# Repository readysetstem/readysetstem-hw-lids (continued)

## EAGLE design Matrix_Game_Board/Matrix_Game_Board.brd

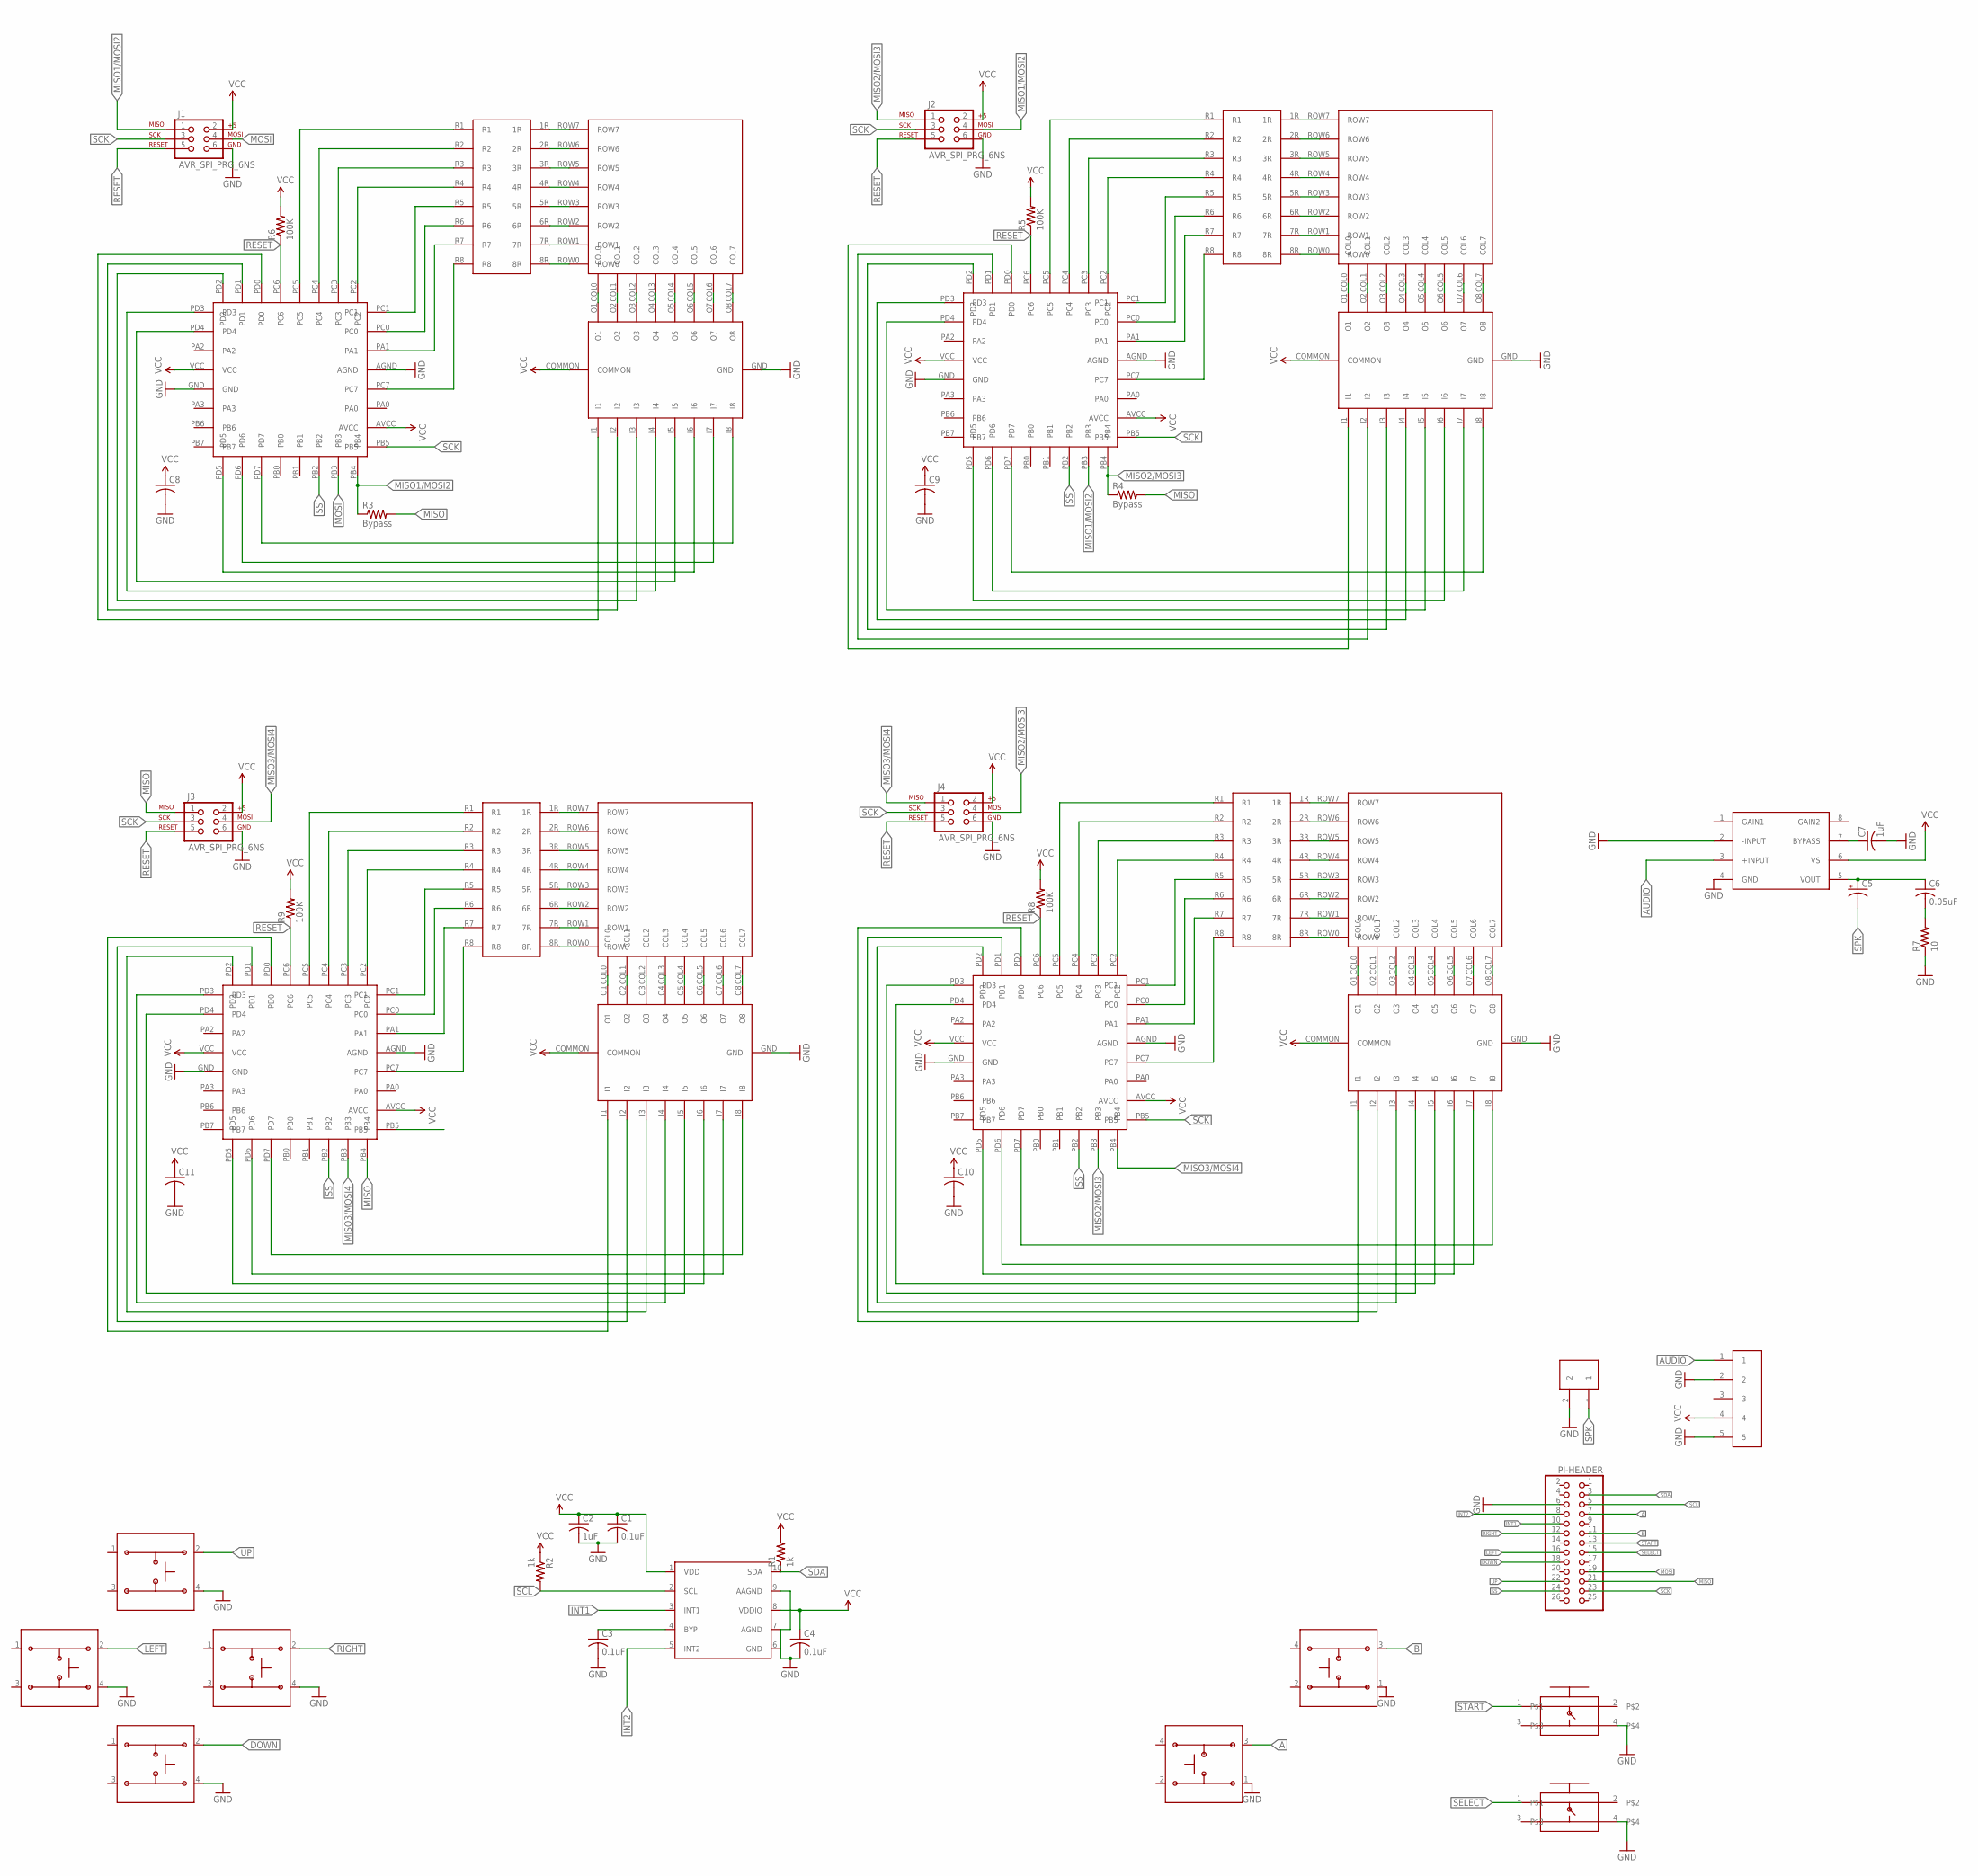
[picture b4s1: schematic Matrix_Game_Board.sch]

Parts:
C1, C3, C4: 0.1uF; C0603
C2, C7: 1uF; C0603
C5: CPOL-US153CLV-0605; 153CLV-0605
C6: 0.05uF; C0603
C8, C9, C10, C11: C-USC0603; C0603
J1, J2, J3, J4: AVR_SPI_PRG_6NS; 2X3-NS
PI-HEADER: PINHD-2X13; 2X13
R1, R2: 1k; R0603
R3, R4: Bypass; R0603
R5, R6, R8, R9: 100K; R0603
R7: 10; R0603
U$1, U$3, U$8, U$13: 8X8_LED_MATRIX
U$2, U$7, U$12, U$16: RES_ARRAY
U$4, U$5, U$10, U$14: ULN2803AFWG
U$6, U$9, U$11, U$15: ATTINY48
U$17, U$18, U$19, U$20, U$21, U$22: 12X12MM_BUTTON
U$23: MMA8653FCR1
U$24, U$26: SMDTACTILE
U$25: LM386
U$29: DF3_1X2
U$30: DF3_1X5

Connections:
A: PI-HEADER.7, U$22.3
AUDIO: U$25.3 (+INPUT), U$30.1
B: PI-HEADER.11, U$21.3
DOWN: PI-HEADER.18, U$20.2
GND: C1.2, C2.2, C3.2, C4.2, C7.2, C8.2, C9.2, C10.2, C11.2, J1.6, J2.6, J3.6, J4.6, PI-HEADER.6, R7.1, U$4.GND, U$5.GND, U$6.AGND, U$6.GND, U$9.AGND, U$9.GND, U$10.GND, U$11.AGND, U$11.GND, U$14.GND, U$15.AGND, U$15.GND, U$17.4, U$18.4, U$19.4, U$20.4, U$21.1, U$22.1, U$23.6 (GND), U$23.7 (AGND), U$23.9 (AAGND), U$24.4, U$25.2 (-INPUT), U$25.4 (GND), U$26.4, U$29.2, U$30.2, U$30.5
INT1: PI-HEADER.10, U$23.3 (INT1)
INT2: PI-HEADER.8, U$23.5 (INT2)
LEFT: PI-HEADER.16, U$18.2
MISO: J3.1, PI-HEADER.21, R3.2, R4.2, U$11.PB4
MISO1/MOSI2: J1.1, J2.4, R3.1, U$6.PB3, U$9.PB4
MISO2/MOSI3: J2.1, J4.4, R4.1, U$6.PB4, U$15.PB3
MISO3/MOSI4: J3.4, J4.1, U$11.PB3, U$15.PB4
MOSI: J1.4, PI-HEADER.19, U$9.PB3
unnamed: U$1.COL0, U$5.O1
unnamed: U$1.COL1, U$5.O2
unnamed: U$1.COL2, U$5.O3
unnamed: U$1.COL3, U$5.O4
unnamed: U$1.COL4, U$5.O5
unnamed: U$1.COL5, U$5.O6
unnamed: U$1.COL6, U$5.O7
unnamed: U$1.COL7, U$5.O8
unnamed: U$1.ROW7, U$2.1R
unnamed: U$1.ROW6, U$2.2R
unnamed: U$1.ROW5, U$2.3R
unnamed: U$1.ROW4, U$2.4R
unnamed: U$1.ROW3, U$2.5R
unnamed: U$1.ROW2, U$2.6R
unnamed: U$1.ROW1, U$2.7R
unnamed: U$1.ROW0, U$2.8R
unnamed: U$5.I1, U$9.PD0
unnamed: U$5.I2, U$9.PD1
unnamed: U$5.I3, U$9.PD2
unnamed: U$5.I4, U$9.PD3
unnamed: U$5.I5, U$9.PD4
unnamed: U$5.I6, U$9.PD5
unnamed: U$5.I7, U$9.PD6
unnamed: U$5.I8, U$9.PD7
unnamed: U$2.R7, U$9.PA1
unnamed: U$2.R8, U$9.PC7
unnamed: U$2.R6, U$9.PC0
unnamed: U$2.R5, U$9.PC1
unnamed: U$2.R4, U$9.PC2
unnamed: U$2.R3, U$9.PC3
unnamed: U$2.R2, U$9.PC4
unnamed: U$2.R1, U$9.PC5
unnamed: C7.1, U$25.7 (BYPASS)
unnamed: C3.1, U$23.4 (BYP)
unnamed: C5.+, C6.1, U$25.5 (VOUT)
unnamed: U$3.COL0, U$4.O1
unnamed: C6.2, R7.2
unnamed: U$3.COL1, U$4.O2
unnamed: U$3.COL2, U$4.O3
unnamed: U$3.COL3, U$4.O4
unnamed: U$3.COL4, U$4.O5
unnamed: U$3.COL5, U$4.O6
unnamed: U$3.COL6, U$4.O7
unnamed: U$3.COL7, U$4.O8
unnamed: U$3.ROW7, U$7.1R
unnamed: U$3.ROW6, U$7.2R
unnamed: U$3.ROW5, U$7.3R
unnamed: U$3.ROW4, U$7.4R
unnamed: U$3.ROW3, U$7.5R
unnamed: U$3.ROW2, U$7.6R
unnamed: U$3.ROW1, U$7.7R
unnamed: U$3.ROW0, U$7.8R
unnamed: U$4.I1, U$6.PD0
unnamed: U$4.I2, U$6.PD1
unnamed: U$4.I3, U$6.PD2
unnamed: U$4.I4, U$6.PD3
unnamed: U$4.I5, U$6.PD4
unnamed: U$4.I6, U$6.PD5
unnamed: U$4.I7, U$6.PD6
unnamed: U$4.I8, U$6.PD7
unnamed: U$6.PA1, U$7.R7
unnamed: U$6.PC7, U$7.R8
unnamed: U$6.PC0, U$7.R6
unnamed: U$6.PC1, U$7.R5
unnamed: U$6.PC2, U$7.R4
unnamed: U$6.PC3, U$7.R3
unnamed: U$6.PC4, U$7.R2
unnamed: U$6.PC5, U$7.R1
unnamed: U$15.PA1, U$16.R7
unnamed: U$8.COL0, U$10.O1
unnamed: U$8.COL1, U$10.O2
unnamed: U$8.COL2, U$10.O3
unnamed: U$8.COL3, U$10.O4
unnamed: U$8.COL4, U$10.O5
unnamed: U$8.COL5, U$10.O6
unnamed: U$8.COL6, U$10.O7
unnamed: U$8.COL7, U$10.O8
unnamed: U$8.ROW7, U$12.1R
unnamed: U$8.ROW6, U$12.2R
unnamed: U$8.ROW5, U$12.3R
unnamed: U$8.ROW4, U$12.4R
unnamed: U$8.ROW3, U$12.5R
unnamed: U$8.ROW2, U$12.6R
unnamed: U$8.ROW1, U$12.7R
unnamed: U$8.ROW0, U$12.8R
unnamed: U$10.I1, U$11.PD0
unnamed: U$10.I2, U$11.PD1
unnamed: U$10.I3, U$11.PD2
unnamed: U$10.I4, U$11.PD3
unnamed: U$10.I5, U$11.PD4
unnamed: U$10.I6, U$11.PD5
unnamed: U$10.I7, U$11.PD6
unnamed: U$10.I8, U$11.PD7
unnamed: U$11.PA1, U$12.R7
unnamed: U$11.PC7, U$12.R8
unnamed: U$11.PC0, U$12.R6
unnamed: U$11.PC1, U$12.R5
unnamed: U$11.PC2, U$12.R4
unnamed: U$11.PC3, U$12.R3
unnamed: U$11.PC4, U$12.R2
unnamed: U$11.PC5, U$12.R1
unnamed: U$15.PC7, U$16.R8
unnamed: U$13.COL0, U$14.O1
unnamed: U$13.COL1, U$14.O2
unnamed: U$13.COL2, U$14.O3
unnamed: U$13.COL3, U$14.O4
unnamed: U$13.COL4, U$14.O5
unnamed: U$13.COL5, U$14.O6
unnamed: U$13.COL6, U$14.O7
unnamed: U$13.COL7, U$14.O8
unnamed: U$13.ROW7, U$16.1R
unnamed: U$13.ROW6, U$16.2R
unnamed: U$13.ROW5, U$16.3R
unnamed: U$13.ROW4, U$16.4R
unnamed: U$13.ROW3, U$16.5R
unnamed: U$13.ROW2, U$16.6R
unnamed: U$13.ROW1, U$16.7R
unnamed: U$13.ROW0, U$16.8R
unnamed: U$14.I1, U$15.PD0
unnamed: U$14.I2, U$15.PD1
unnamed: U$14.I3, U$15.PD2
unnamed: U$14.I4, U$15.PD3
unnamed: U$14.I5, U$15.PD4
unnamed: U$14.I6, U$15.PD5
unnamed: U$14.I7, U$15.PD6
unnamed: U$14.I8, U$15.PD7
unnamed: U$15.PC0, U$16.R6
unnamed: U$15.PC1, U$16.R5
unnamed: U$15.PC2, U$16.R4
unnamed: U$15.PC3, U$16.R3
unnamed: U$15.PC4, U$16.R2
unnamed: U$15.PC5, U$16.R1
RESET: J1.5, J2.5, J3.5, J4.5, R5.1, R6.1, R8.1, R9.1, U$6.PC6, U$9.PC6, U$11.PC6, U$15.PC6
RIGHT: PI-HEADER.12, U$19.2
SCK: J1.3, J2.3, J3.3, J4.3, PI-HEADER.23, U$6.PB5, U$9.PB5, U$11.PB5, U$15.PB5
SCL: PI-HEADER.5, R2.2, U$23.2 (SCL)
SDA: PI-HEADER.3, R1.1, U$23.10 (SDA)
SELECT: PI-HEADER.15, U$26.1
SPK: C5.-, U$29.1
SS: PI-HEADER.24, U$6.PB2, U$9.PB2, U$11.PB2, U$15.PB2
START: PI-HEADER.13, U$24.1
UP: PI-HEADER.22, U$17.2
VCC: C1.1, C2.1, C4.1, C8.1, C9.1, C10.1, C11.1, J1.2, J2.2, J3.2, J4.2, R1.2, R2.1, R5.2, R6.2, R8.2, R9.2, U$4.COMMON, U$5.COMMON, U$6.AVCC, U$6.VCC, U$9.AVCC, U$9.VCC, U$10.COMMON, U$11.AVCC, U$11.VCC, U$14.COMMON, U$15.AVCC, U$15.VCC, U$23.1 (VDD), U$23.8 (VDDIO), U$25.6 (VS), U$30.4

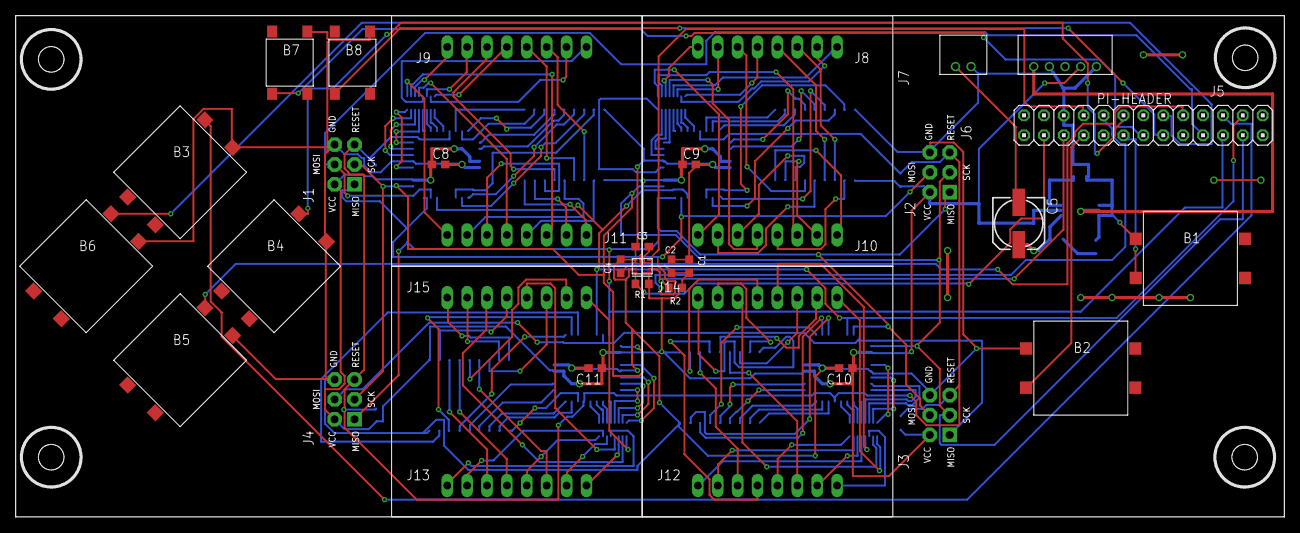
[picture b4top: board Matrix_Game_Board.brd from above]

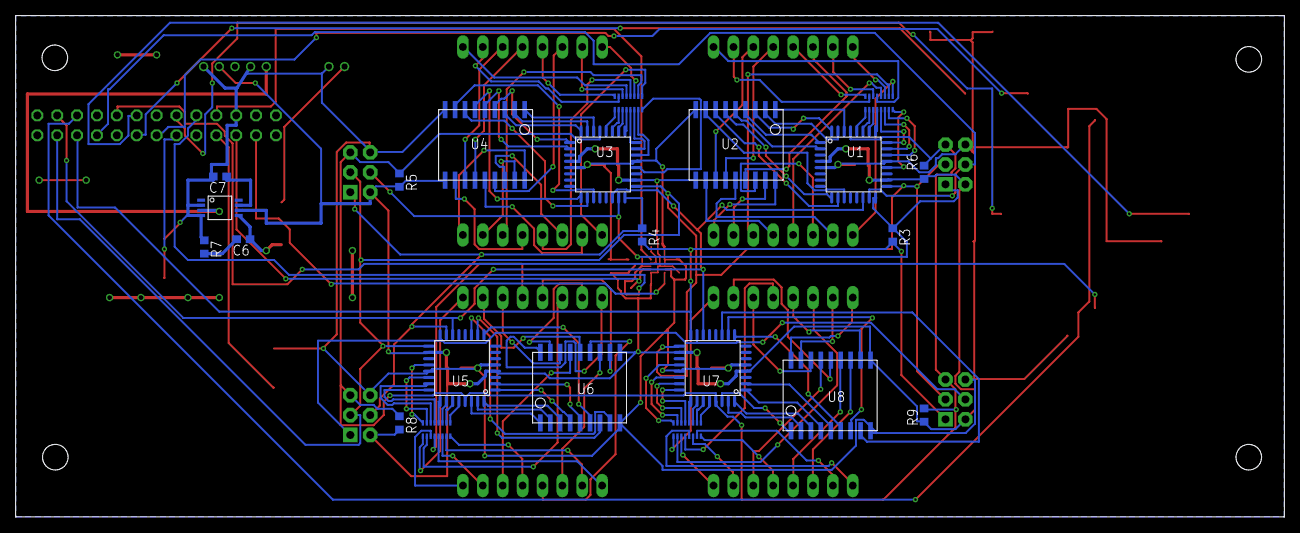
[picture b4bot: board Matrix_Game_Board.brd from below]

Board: 2 copper layers, 162.0 x 64.0 mm, 53 parts (22 on the bottom side), 156 nets.

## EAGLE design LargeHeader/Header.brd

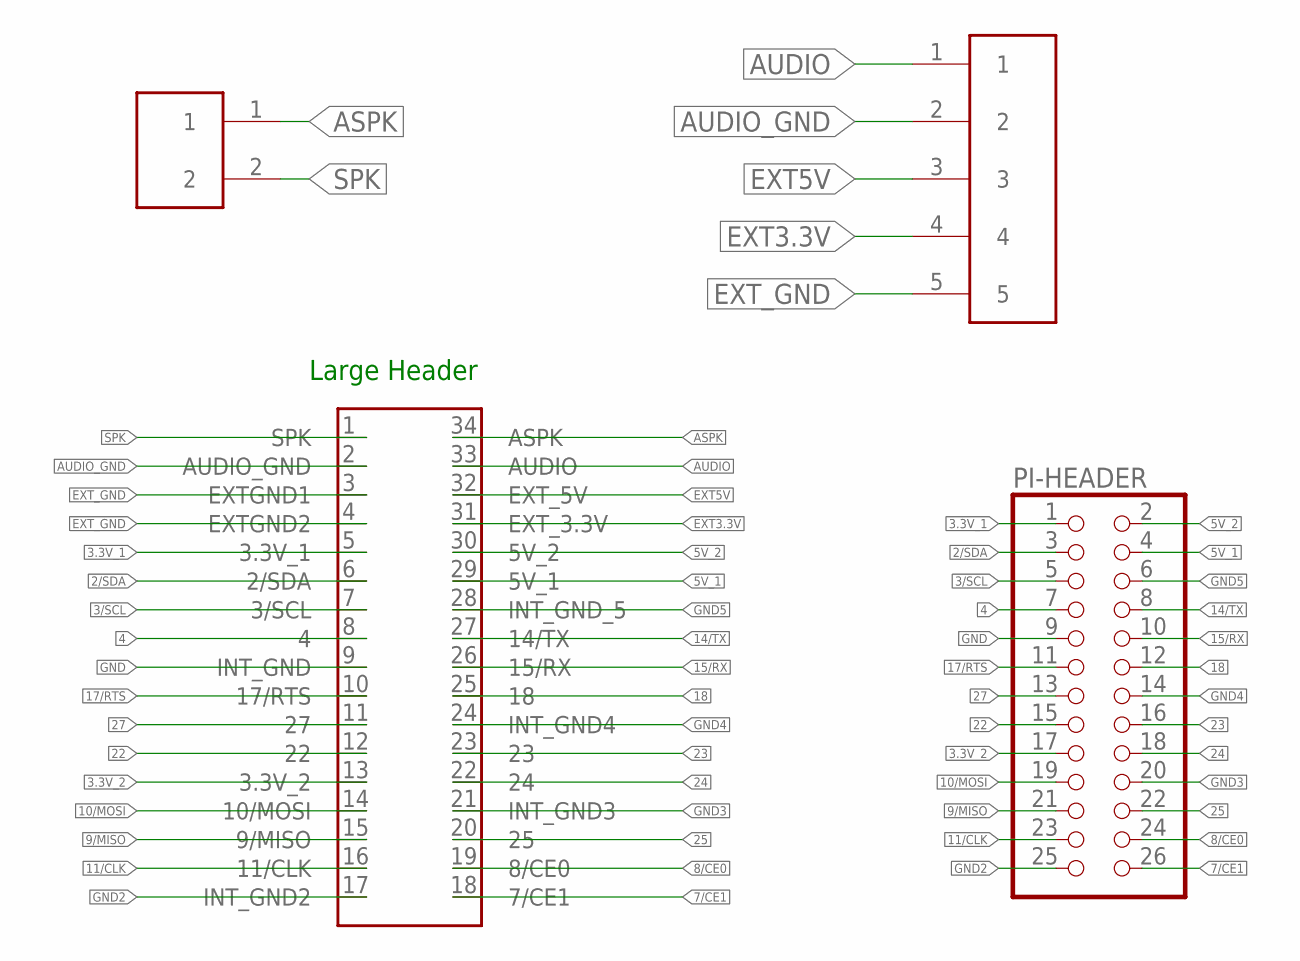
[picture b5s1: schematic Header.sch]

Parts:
PI-HEADER: PINHD-2X13; 2X13
U$1: 2X17HEADER; 2X32HEADER
U$2: DF3_1X5
U$4: DF3_1X2

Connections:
2/SDA: PI-HEADER.3, U$1.6 (2/SDA)
3.3V_1: PI-HEADER.1, U$1.5 (3.3V_1)
3.3V_2: PI-HEADER.17, U$1.13 (3.3V_2)
3/SCL: PI-HEADER.5, U$1.7 (3/SCL)
4: PI-HEADER.7, U$1.8 (4)
5V_1: PI-HEADER.4, U$1.29 (5V_1)
5V_2: PI-HEADER.2, U$1.30 (5V_2)
7/CE1: PI-HEADER.26, U$1.18 (7/CE1)
8/CE0: PI-HEADER.24, U$1.19 (8/CE0)
9/MISO: PI-HEADER.21, U$1.15 (9/MISO)
10/MOSI: PI-HEADER.19, U$1.14 (10/MOSI)
11/CLK: PI-HEADER.23, U$1.16 (11/CLK)
14/TX: PI-HEADER.8, U$1.27 (14/TX)
15/RX: PI-HEADER.10, U$1.26 (15/RX)
17/RTS: PI-HEADER.11, U$1.10 (17/RTS)
18: PI-HEADER.12, U$1.25 (18)
22: PI-HEADER.15, U$1.12 (22)
23: PI-HEADER.16, U$1.23
24: PI-HEADER.18, U$1.22 (24)
25: PI-HEADER.22, U$1.20 (25)
27: PI-HEADER.13, U$1.11 (27)
ASPK: U$1.34 (ASPK), U$4.1
AUDIO: U$1.33 (AUDIO), U$2.1
AUDIO_GND: U$1.2 (AUDIO_GND), U$2.2
EXT3.3V: U$1.31 (EXT_3.3V), U$2.4
EXT5V: U$1.32 (EXT_5V), U$2.3
EXT_GND: U$1.3 (EXTGND1), U$1.4 (EXTGND2), U$2.5
GND: PI-HEADER.9, U$1.9 (INT_GND)
GND2: PI-HEADER.25, U$1.17 (INT_GND2)
GND3: PI-HEADER.20, U$1.21 (INT_GND3)
GND4: PI-HEADER.14, U$1.24 (INT_GND4)
GND5: PI-HEADER.6, U$1.28 (INT_GND_5)
SPK: U$1.1 (SPK), U$4.2

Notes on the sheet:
Large Header

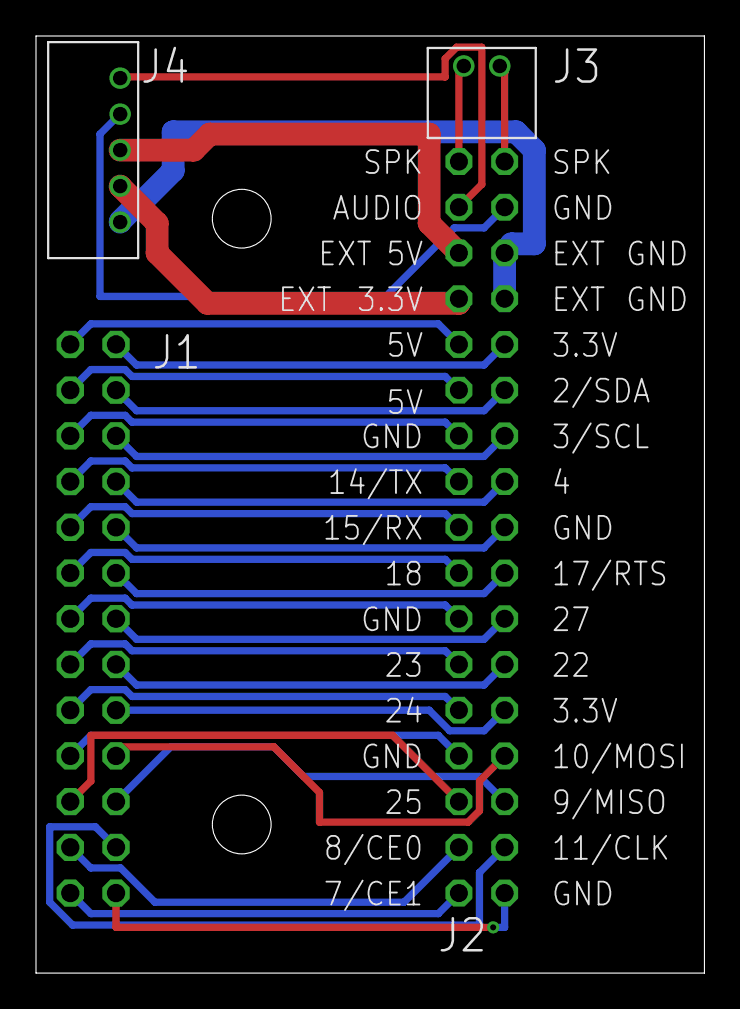
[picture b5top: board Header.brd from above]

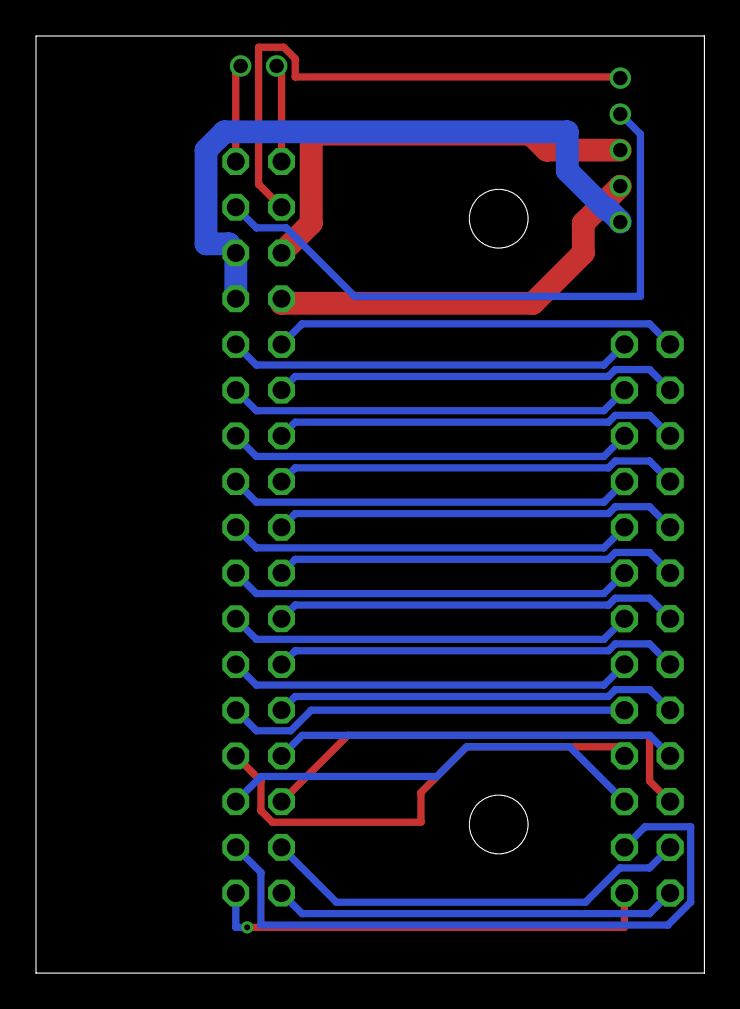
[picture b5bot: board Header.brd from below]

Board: 2 copper layers, 37.1 x 52.1 mm, 4 parts (4 on the bottom side), 33 nets.

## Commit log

2014-06-06 Added AL License to all applicable files
2014-06-26 Added BOM for header PCB
2014-07-18 Fixed 5V text misalignment
2014-07-22 Removed bottom layer silk screen
2014-07-22 Added matrix brd and sch
2014-07-22 Added files to folder Matrix_Game_Board
2014-07-25 Shifted text to not be blocked by header
2014-07-25 Added start and select buttons to matrix board and moved accelerometer to the middle of the board
2014-07-25 Corrected some net names on Gamer PCB
2014-07-25 Corrected some more net names on Gamer PCB
2014-07-25 Changed resistors to 0603 on gamer PCB
2014-08-01 Moved start and select, moved pi header down to make screws in 2x6in square
2014-08-07 Changed to right angle headers for power and speaker
2014-08-15 Inverted bottom row of matrices, routed CS, added ground plane
2014-08-28 Moved buttons down, moved large capacitor to top of board
2014-12-30 renamed LargeHeader -> HeaderConnectorBoard
2014-12-30 Model A/B Plus compatibility with major simplification
    Simplified header connetor to ONLY be a Raspberry Pi header connectorizer -
    that is, it no longer takes speaker or audio (or the now deprecated USB power
    adapter). Speaker and audio will be handled with simpler cables to the
    breadboard. So, now the header only has 2 connectors: a header to the RasPi,
    and a header for breadboard connections.
    Also, a total redo of the labeling to have a much more clear grid layout,
2015-01-04 HeaderConnectorBoard - Increased font size of some labels
2015-01-04 HeaderConnectorBoard - Adjust font sizes/type
2015-01-22 lid connector - changed size and mounting for top mounting on lid
    New connector board will be mounted on top (used to be bottom) of RaspberrySTEM
    Lid, with an extra arcrylic spacer in between.
2015-01-22 lic connector - adjustments to fit with acrylic
2015-01-22 lid connector - moved/rotated logo
    It previously overlapped with one of the headers.
2015-01-22 lid connector - added ALT/GPIO labelling
2015-02-20 lid connector - Readjust mounting holes. Rev-01a.
    adjustments to allow screw head clearance for board headers, and to clear silkscreen.
2015-03-19 lid connector - BOM
2015-03-20 gamer - preliminary BOM
2015-04-10 Gamer - Rename Gamer board
2015-04-14 gamer - Starting complete redo of Gamer
2015-04-15 lid connector - created gerbers
2015-04-15 lid conn - Added board fab notes images
2015-04-15 PCBs - Added gitignores
2015-04-15 Gamer - Added generic Makefile
2015-04-15 gamer - Work in progress
2015-04-16 gamer - Duplicated matrices (not laid out)
2015-04-16 gamer - intial layout of all matrix parts
2015-04-16 gamer - rejiggered PROG connectors
2015-04-16 gamer - properly chained MISO/MOSI through LED matrices
2015-04-16 gamer - fully routed, first attempt
    Will need to be rerouted, if middle mounting holes are added.
2015-04-17 gamer - partial routing, with ground plane and vias, and some hand routing
2015-04-17 gamer - more manual routing
2015-04-17 gamer - hand route accelerometer
2015-04-17 gamer - auto route 100%
2015-04-17 gamer - Added logo and other text
2015-04-17 gamer - Moved text that conflicted with stop mask
2015-04-17 gamer - Order of SPI chain was backwards
2015-04-17 gamer - ERC passes (with many okay warnings)
2015-04-17 gamer - Rerouted 100%
2015-04-18 gamer - main header was flipped. Flipped and rerouted 100%.
2015-05-04 gamer - first new protoype fixes... Unrouted.
    - RaspberrySTEM GAMER name obscured by header
    - mounting holes
    - header pins flipped
2015-05-04 gamer - rerouted. remasked mounting holes around bottom gnd plane
2015-05-05 gamer - rev up, added accel silkscreen, other fixes
2015-05-05 gamer - updated BOM and silkscreen
2015-05-05 gamer - added gerbers
2015-05-13 gamer - Added EEPROM, unplaced and unrouted.
2015-05-13 gamer - eeprom placed and routed
2015-08-03 Removed LICENSE for HW projects. Will reevaluate in the future.
2016-08-05 Lid Conn - Updated versions and product name
2016-08-05 Lid conn - added POWER LED
2016-08-05 Lid conn - RaspSTEM logo -> Ready Set STEM logo
2016-08-08 updated fab notes files (copied from readysetstem-hw-base)
    fab notes now maintained here
2016-08-08 updtaed gerbers
2016-08-20 HeaderConnectorBoard BOM update
2016-09-07 Lid Conn - updated part numbers
2016-09-07 lid conn - labels were flipped (and thus power led broken)
    JP1/JP2 had all labelled flipped, which previously was a don't care because the connectors were
    connected straight thru, and no labels were used. When power was added, it was to the wrong pins
    because the labels were wrong. Both are now fixed.
2016-09-13 MiniConnectorBoard - Copied from HeaderConnectorBoard
2016-09-14 MiniConnectorBoard - first cut
2016-09-14 MiniConnectorBoard - updated gerbers
2016-09-27 HeaderConnectorBoard - updated board-*.jpg photos
2016-09-27 MiniConnectorBoard - added board-*.jpg photos
2016-09-27 HeaderConnectorBoard - removed logo which is not exporting correctly
    Centered copyright. Logo is exporting excessively large in gerbers. Need to fix.
2016-09-28 HeaderConnectorBoard - updated logo
    previous logo was not gerber exportable
2016-09-28 HeaderConnectorBoard - updated gerbers
2016-09-28 HeaderConnectorBoard - Updated board to Rev-02b
2016-09-28 HeaderConnectorBoard - Added LED part orientation
2016-09-28 MiniConnectorBoard - removed power, added logo, Rev-01b
2016-09-28 MiniConnectorBoard - updated BOM and annotations
